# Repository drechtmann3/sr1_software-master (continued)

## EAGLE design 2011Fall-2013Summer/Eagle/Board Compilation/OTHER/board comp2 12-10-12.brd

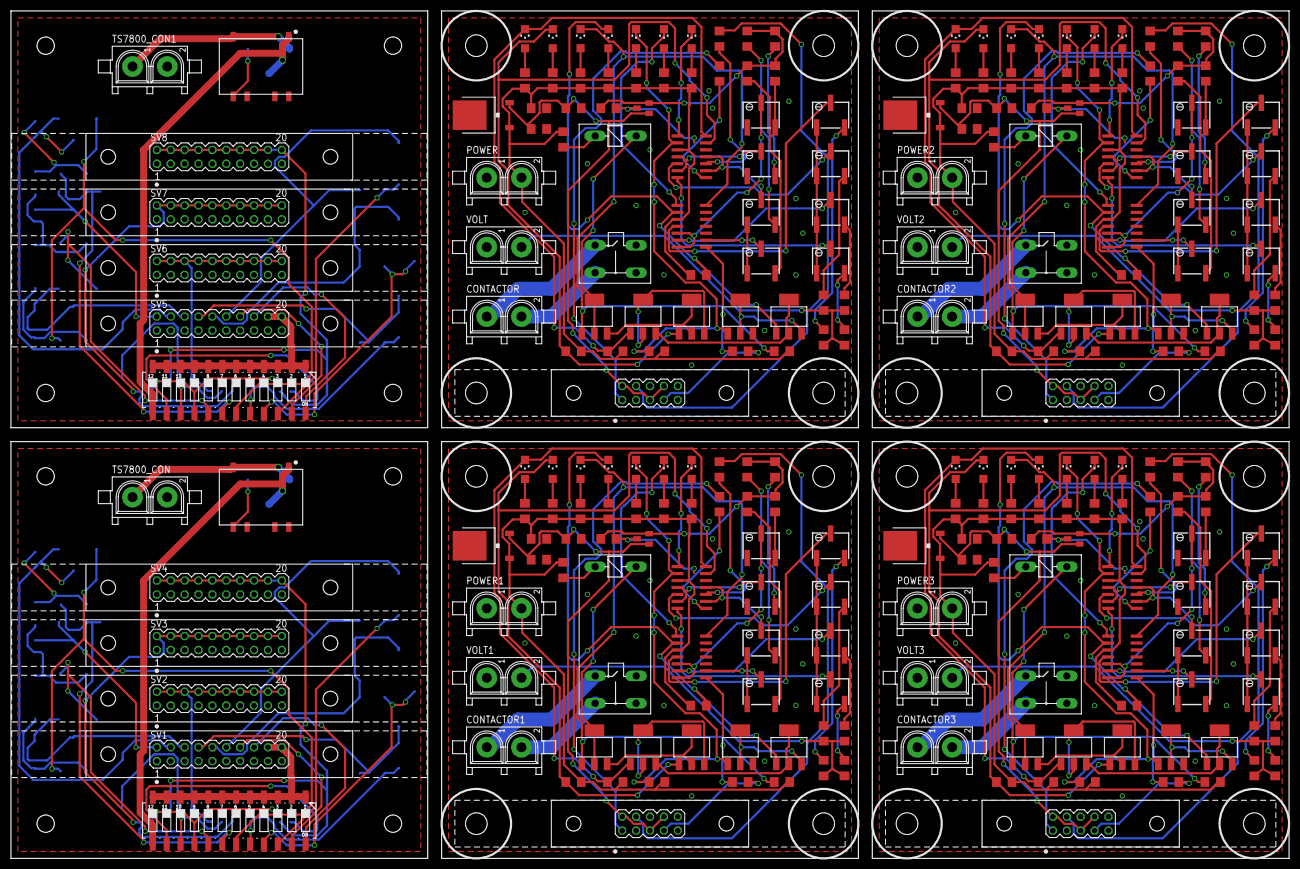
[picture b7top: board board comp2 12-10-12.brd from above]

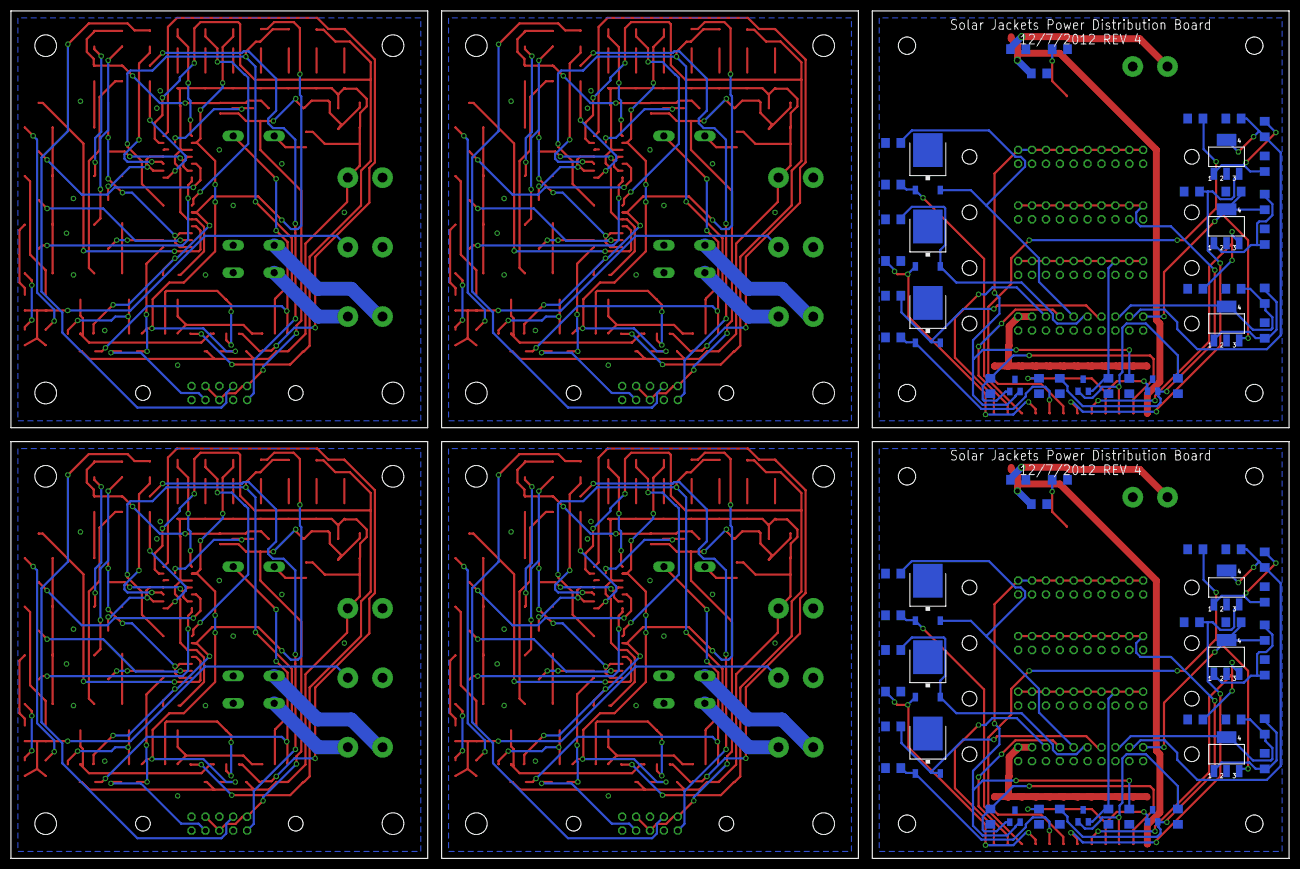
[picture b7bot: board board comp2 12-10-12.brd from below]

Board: 2 copper layers, 233.7 x 154.9 mm, 314 parts (72 on the bottom side), 252 nets.

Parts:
3V1, 3V2, 3V3, 3V4, 3V5, 3V6, 3V7, 3V8, 3V9, 3V10: MAX6103; SOT23
317CAP1, 317CAP3, 317CAP4, 317CAP6, 317CAP9, 317CAP11: .33uF; C1206
317CAP2, 317CAP5, 317CAP7, 317CAP8, 317CAP10, 317CAP12, 6103CAP1, 6103CAP2, 6103CAP3, 6103CAP4, 6103CAP5, 6103CAP6, 6103CAP7, 6103CAP8, 6103CAP9, 6103CAP10, 6103CAP11, 6103CAP12, 6103CAP13, 6103CAP14, 6103CAP15, 6103CAP16, 6103CAP17, 6103CAP18, 6103CAP19, 6103CAP20, 7805CAP1, 7805CAP2, 7805CAP3, 7805CAP4, 7805CAP5, 7805CAP6, 7805CAP7, 7805CAP8: 1uF; C1206
C1, C2, C3, C4, C5, C6, C7, C8, C9, C10, C11, C12: 1uF; C1206
CONTACTOR, CONTACTOR1, CONTACTOR2, CONTACTOR3: 350428-1
CURRENT_TRIM, CURRENT_TRIM1, CURRENT_TRIM2, CURRENT_TRIM3: 1k; RTRIMTS63Y
IC1, IC2, IC3, IC4, IC5, IC6: LM317; SOT223
IC7, IC9, IC10, IC12, IC13, IC15, IC16, IC18: LM339D; SO14
IC8, IC11, IC14, IC17: 7805DT; TO252
K1, K2, K3, K4: G2REA
OVERCURRENT, OVERCURRENT1, OVERCURRENT2, OVERCURRENT3: CHIPLED_1206
OVERCURRENT_FET, OVERCURRENT_FET1, OVERCURRENT_FET2, OVERCURRENT_FET3: N-HEXFET-2D_SOT232-; SOT223
OVERTEMP1, OVERTEMP2, OVERTEMP3, OVERTEMP4, OVERTEMP5, OVERTEMP6, OVERTEMP7, OVERTEMP8: CHIPLED_1206
OVERTEMP1_FET, OVERTEMP1_FET1, OVERTEMP1_FET2, OVERTEMP1_FET3, OVERTEMP2_FET, OVERTEMP2_FET1, OVERTEMP2_FET2, OVERTEMP2_FET3: N-HEXFET-2D_SOT232-; SOT223
OVERVOLT, OVERVOLT1, OVERVOLT2, OVERVOLT3: CHIPLED_1206
OVERVOLT_FET, OVERVOLT_FET1, OVERVOLT_FET2, OVERVOLT_FET3: N-HEXFET-2D_SOT232-; SOT223
OVERVOLT_WARN, OVERVOLT_WARN1, OVERVOLT_WARN2, OVERVOLT_WARN3: CHIPLED_1206
OVER_CRIT, OVER_CRIT1, OVER_CRIT2, OVER_CRIT3: 10k; RTRIMTS63Y
OVER_TRIM, OVER_TRIM1, OVER_TRIM2, OVER_TRIM3: 1k; RTRIMTS63Y
OVER_WARN, OVER_WARN1, OVER_WARN2, OVER_WARN3: 10k; RTRIMTS63Y
POWER, POWER1, POWER2, POWER3: 350428-1
PWR_1, PWR_2, PWR_3, PWR_4, PWR_5, PWR_6: 7805DT; TO252
R1, R3, R5, R7, R9, R11: 220; R1206
R2, R4, R6, R8, R10, R12: 361; R1206
R13, R14, R29, R30, R37, R38, R53, R54, R61, R62, R77, R78, R85, R86, R101, R102: 100k; R1206
R15, R16, R17, R18, R24, R32, R33, R39, R40, R41, R42, R48, R56, R57, R63, R64, R65, R66, R72, R80, R81, R87, R88, R89, R90, R96, R104, R105: 100; R1206
R19, R20, R21, R22, R31, R34, R35, R36, R43, R44, R45, R46, R55, R58, R59, R60, R67, R68, R69, R70, R79, R82, R83, R84, R91, R92, R93, R94, R103, R106, R107, R108: 1k; R1206
R23, R25, R26, R27, R28, R47, R49, R50, R51, R52, R71, R73, R74, R75, R76, R95, R97, R98, R99, R100: 10k; R1206
S1, S2: 219-12; CTS-219-12
SV1, SV2, SV3, SV4, SV5, SV6, SV7, SV8: AMPLATCH-20; MA10-2
SV9, SV10, SV11, SV12: AMP_LATCH_10; MA05-2
TEMP_TRIM, TEMP_TRIM1, TEMP_TRIM2, TEMP_TRIM3: 1k; RTRIMTS63Y
TS7800_CON, TS7800_CON1: 350759-4
U$1, U$2: V7805
UNDERVOLT, UNDERVOLT1, UNDERVOLT2, UNDERVOLT3: CHIPLED_1206
UNDERVOLT_FET, UNDERVOLT_FET1, UNDERVOLT_FET2, UNDERVOLT_FET3: N-HEXFET-2D_SOT232-; SOT223
UNDERVOLT_WARN, UNDERVOLT_WARN1, UNDERVOLT_WARN2, UNDERVOLT_WARN3: CHIPLED_1206
UNDER_CRIT, UNDER_CRIT1, UNDER_CRIT2, UNDER_CRIT3: 10k; RTRIMTS63Y
UNDER_TRIM, UNDER_TRIM1, UNDER_TRIM2, UNDER_TRIM3: 1k; RTRIMTS63Y
UNDER_WARN, UNDER_WARN1, UNDER_WARN2, UNDER_WARN3: 10k; RTRIMTS63Y
V7805_C1, V7805_C2, V7805_C3, V7805_C4, V7805_C5, V7805_C6: 1uF; C1206
VOLT, VOLT1, VOLT2, VOLT3: 350428-1

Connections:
3.3V1: 317CAP8.1, IC4.4, R7.1, SV1.6
3.3V1_EN: 317CAP3.1, IC4.3, S1.19
3.3V1_EN1: 317CAP1.1, IC1.3, S2.19
3.3V2: 317CAP10.1, IC5.4, R9.1, SV1.4
3.3V2_EN: 317CAP9.1, IC5.3, S1.18
3.3V2_EN1: 317CAP4.1, IC2.3, S2.18
3.3V3: 317CAP12.1, IC6.4, R11.1, SV1.2
3.3V3_EN: 317CAP11.1, IC6.3, S1.17
3.3V3_EN1: 317CAP6.1, IC3.3, S2.17
3.3V4: 317CAP7.1, IC3.4, R5.1, SV5.2
3.3V5: 317CAP2.1, IC1.4, R1.1, SV5.6
3.3V6: 317CAP5.1, IC2.4, R3.1, SV5.4
5V: 3V7.1, 6103CAP13.1, 7805CAP2.1, IC8.2, SV9.2, SV9.5, SV9.8
5V1: C2.1, PWR_1.2, SV1.12
5V1_EN: C1.1, PWR_1.1, S1.22
5V1_EN1: C7.1, PWR_4.1, S2.22
5V2: C4.1, PWR_2.2, SV1.10
5V2_EN: C3.1, PWR_2.1, S1.21
5V2_EN1: C9.1, PWR_5.1, S2.21
5V3: C6.1, PWR_3.2, SV1.8
5V3_EN: C5.1, PWR_3.1, S1.20
5V3_EN1: C12.1, PWR_6.1, S2.20
5V4: C11.1, PWR_6.2, SV5.8
5V5: C10.1, PWR_5.2, SV5.10
5V6: C8.1, PWR_4.2, SV5.12
5V7: 3V8.1, 6103CAP15.1, 7805CAP3.1, IC11.2, SV10.2, SV10.5, SV10.8
5V8: 3V9.1, 6103CAP17.1, 7805CAP5.1, IC14.2, SV11.2, SV11.5, SV11.8
5V9: 3V10.1, 6103CAP19.1, 7805CAP7.1, IC17.2, SV12.2, SV12.5, SV12.8
12V: S1.1, S1.2, S1.3, S1.4, S1.5, S1.6, S1.7, S1.8, S1.9, S1.10, S1.11, S1.12, SV1.18, SV1.20
12V1: S2.1, S2.2, S2.3, S2.4, S2.5, S2.6, S2.7, S2.8, S2.9, S2.10, S2.11, S2.12, SV5.18, SV5.20
12V1_EN: S1.24, SV1.16
12V1_EN1: S2.24, SV5.16
12V2: 7805CAP1.1, IC7.3, IC8.1, IC9.3, POWER.2, R19.2, R20.2, R21.2, R22.2, R23.2, R24.2, R25.2, R26.2, R27.2, R28.2, R34.2, R35.2, R36.2
12V2_EN: S1.23, SV1.14
12V2_EN1: S2.23, SV5.14
12V3: 7805CAP4.1, IC10.3, IC11.1, IC12.3, POWER1.2, R43.2, R44.2, R45.2, R46.2, R47.2, R48.2, R49.2, R50.2, R51.2, R52.2, R58.2, R59.2, R60.2
12V4: 7805CAP6.1, IC13.3, IC14.1, IC15.3, POWER2.2, R67.2, R68.2, R69.2, R70.2, R71.2, R72.2, R73.2, R74.2, R75.2, R76.2, R82.2, R83.2, R84.2
12V5: 7805CAP8.1, IC16.3, IC17.1, IC18.3, POWER3.2, R91.2, R92.2, R93.2, R94.2, R95.2, R96.2, R97.2, R98.2, R99.2, R100.2, R106.2, R107.2, R108.2
96V: R13.2, R14.2, R29.2, R30.2, VOLT.2
96V1: R37.2, R38.2, R53.2, R54.2, VOLT1.2
96V2: R61.2, R62.2, R77.2, R78.2, VOLT2.2
96V3: R85.2, R86.2, R101.2, R102.2, VOLT3.2
CONTACTOR_IN: CONTACTOR.2, K1.S
CONTACTOR_IN1: CONTACTOR1.2, K2.S
CONTACTOR_IN2: CONTACTOR2.2, K3.S
CONTACTOR_IN3: CONTACTOR3.2, K4.S
CONTACTOR_OUT: CONTACTOR.1, K1.P
CONTACTOR_OUT1: CONTACTOR1.1, K2.P
CONTACTOR_OUT2: CONTACTOR2.1, K3.P
CONTACTOR_OUT3: CONTACTOR3.1, K4.P
CURRENT: R31.2, SV9.7
CURRENT1: R55.2, SV10.7
CURRENT2: R79.2, SV11.7
CURRENT3: R103.2, SV12.7
GND: 3V3.3, 3V4.3, 3V5.3, 317CAP3.2, 317CAP8.2, 317CAP9.2, 317CAP10.2, 317CAP11.2, 317CAP12.2, 6103CAP7.2, 6103CAP8.2, 6103CAP9.2, 6103CAP10.2, 6103CAP11.2, 6103CAP12.2, C1.2, C2.2, C3.2, C4.2, C5.2, C6.2, PWR_1.3, PWR_2.3, PWR_3.3, R8.2, R10.2, R12.2, SV1.1, SV1.3, SV1.5, SV1.7, SV1.9, SV1.11, SV1.13, SV1.15, SV1.17, SV1.19, SV2.1, SV2.3, SV2.5, SV2.7, SV2.9, SV2.11, SV2.13, SV2.15, SV2.17, SV2.19, SV3.1, SV3.3, SV3.5, SV3.7, SV3.9, SV3.11, SV3.13, SV3.15, SV3.17, SV3.19, SV4.1, SV4.3, SV4.5, SV4.7, SV4.9, SV4.11, SV4.13, SV4.15, SV4.17, SV4.19, TS7800_CON.2, U$2.7, U$2.9, V7805_C4.2, V7805_C5.2, V7805_C6.2
GND1: 3V1.3, 3V2.3, 3V6.3, 317CAP1.2, 317CAP2.2, 317CAP4.2, 317CAP5.2, 317CAP6.2, 317CAP7.2, 6103CAP1.2, 6103CAP2.2, 6103CAP3.2, 6103CAP4.2, 6103CAP5.2, 6103CAP6.2, C7.2, C8.2, C9.2, C10.2, C11.2, C12.2, PWR_4.3, PWR_5.3, PWR_6.3, R2.2, R4.2, R6.2, SV5.1, SV5.3, SV5.5, SV5.7, SV5.9, SV5.11, SV5.13, SV5.15, SV5.17, SV5.19, SV6.1, SV6.3, SV6.5, SV6.7, SV6.9, SV6.11, SV6.13, SV6.15, SV6.17, SV6.19, SV7.1, SV7.3, SV7.5, SV7.7, SV7.9, SV7.11, SV7.13, SV7.15, SV7.17, SV7.19, SV8.1, SV8.3, SV8.5, SV8.7, SV8.9, SV8.11, SV8.13, SV8.15, SV8.17, SV8.19, TS7800_CON1.2, U$1.7, U$1.9, V7805_C1.2, V7805_C2.2, V7805_C3.2
GND2: 3V7.3, 6103CAP13.2, 6103CAP14.2, 7805CAP1.2, 7805CAP2.2, CURRENT_TRIM.1, IC7.12, IC8.3, IC9.12, OVER_CRIT.1, OVER_TRIM.1, OVER_WARN.1, POWER.1, SV9.3, SV9.6, SV9.9, TEMP_TRIM.1, UNDERVOLT_FET.3, UNDER_CRIT.1, UNDER_TRIM.1, UNDER_WARN.1, VOLT.1
GND3: 3V8.3, 6103CAP15.2, 6103CAP16.2, 7805CAP3.2, 7805CAP4.2, CURRENT_TRIM1.1, IC10.12, IC11.3, IC12.12, OVER_CRIT1.1, OVER_TRIM1.1, OVER_WARN1.1, POWER1.1, SV10.3, SV10.6, SV10.9, TEMP_TRIM1.1, UNDERVOLT_FET1.3, UNDER_CRIT1.1, UNDER_TRIM1.1, UNDER_WARN1.1, VOLT1.1
GND4: 3V9.3, 6103CAP17.2, 6103CAP18.2, 7805CAP5.2, 7805CAP6.2, CURRENT_TRIM2.1, IC13.12, IC14.3, IC15.12, OVER_CRIT2.1, OVER_TRIM2.1, OVER_WARN2.1, POWER2.1, SV11.3, SV11.6, SV11.9, TEMP_TRIM2.1, UNDERVOLT_FET2.3, UNDER_CRIT2.1, UNDER_TRIM2.1, UNDER_WARN2.1, VOLT2.1
GND5: 3V10.3, 6103CAP19.2, 6103CAP20.2, 7805CAP7.2, 7805CAP8.2, CURRENT_TRIM3.1, IC16.12, IC17.3, IC18.12, OVER_CRIT3.1, OVER_TRIM3.1, OVER_WARN3.1, POWER3.1, SV12.3, SV12.6, SV12.9, TEMP_TRIM3.1, UNDERVOLT_FET3.3, UNDER_CRIT3.1, UNDER_TRIM3.1, UNDER_WARN3.1, VOLT3.1
unnamed: U$2.6, V7805_C4.1
unnamed: IC1.1, R1.2, R2.1
unnamed: IC2.1, R3.2, R4.1
unnamed: IC3.1, R5.2, R6.1
unnamed: U$1.6, V7805_C1.1
unnamed: IC7.7, UNDER_WARN.2
unnamed: IC7.5, UNDER_CRIT.2
unnamed: IC7.9, IC7.11, TEMP_TRIM.2
unnamed: R13.1, UNDER_CRIT.3
unnamed: R14.1, UNDER_WARN.3
unnamed: IC7.4, IC7.6, UNDER_TRIM.2
unnamed: IC4.1, R7.2, R8.1
unnamed: IC5.1, R9.2, R10.1
unnamed: IC6.1, R11.2, R12.1
unnamed: R18.1, UNDER_TRIM.3
unnamed: R17.1, TEMP_TRIM.3
unnamed: R19.1, UNDERVOLT.A
unnamed: R20.1, UNDERVOLT_WARN.A
unnamed: OVERTEMP1.A, R21.1
unnamed: OVERTEMP2.A, R22.1
unnamed: IC7.8, R15.1
unnamed: IC7.10, R16.1
unnamed: CURRENT_TRIM.2, IC9.9
unnamed: OVER_WARN.3, R30.1
unnamed: IC9.6, OVER_WARN.2
unnamed: IC9.4, OVER_CRIT.2
unnamed: IC9.5, IC9.7, OVER_TRIM.2
unnamed: OVER_TRIM.3, R33.1
unnamed: CURRENT_TRIM.3, R32.1
unnamed: OVERVOLT.A, R34.1
unnamed: OVERVOLT_WARN.A, R35.1
unnamed: OVERCURRENT.A, R36.1
unnamed: OVER_CRIT.3, R29.1
unnamed: IC9.8, R31.1
unnamed: K1.1, R24.1
unnamed: K1.2, OVERCURRENT_FET.2, OVERCURRENT_FET.4
unnamed: OVERCURRENT_FET.3, OVERTEMP2_FET.2, OVERTEMP2_FET.4
unnamed: OVERTEMP1_FET.2, OVERTEMP1_FET.4, OVERTEMP2_FET.3
unnamed: OVERTEMP1_FET.3, OVERVOLT_FET.2, OVERVOLT_FET.4
unnamed: OVERVOLT_FET.3, UNDERVOLT_FET.2, UNDERVOLT_FET.4
unnamed: IC10.7, UNDER_WARN1.2
unnamed: IC10.5, UNDER_CRIT1.2
unnamed: IC10.9, IC10.11, TEMP_TRIM1.2
unnamed: R37.1, UNDER_CRIT1.3
unnamed: R38.1, UNDER_WARN1.3
unnamed: IC10.4, IC10.6, UNDER_TRIM1.2
unnamed: R42.1, UNDER_TRIM1.3
unnamed: R41.1, TEMP_TRIM1.3
unnamed: R43.1, UNDERVOLT1.A
unnamed: R44.1, UNDERVOLT_WARN1.A
unnamed: OVERTEMP3.A, R45.1
unnamed: OVERTEMP4.A, R46.1
unnamed: IC10.8, R39.1
unnamed: IC10.10, R40.1
unnamed: CURRENT_TRIM1.2, IC12.9
unnamed: OVER_WARN1.3, R54.1
unnamed: IC12.5, IC12.7, OVER_TRIM1.2
unnamed: OVER_TRIM1.3, R57.1
unnamed: CURRENT_TRIM1.3, R56.1
unnamed: OVERVOLT1.A, R58.1
unnamed: OVERVOLT_WARN1.A, R59.1
unnamed: OVERCURRENT1.A, R60.1
unnamed: IC12.6, OVER_WARN1.2
unnamed: IC12.4, OVER_CRIT1.2
unnamed: OVER_CRIT1.3, R53.1
unnamed: IC12.8, R55.1
unnamed: K2.1, R48.1
unnamed: K2.2, OVERCURRENT_FET1.2, OVERCURRENT_FET1.4
unnamed: OVERCURRENT_FET1.3, OVERTEMP2_FET1.2, OVERTEMP2_FET1.4
unnamed: OVERTEMP1_FET1.2, OVERTEMP1_FET1.4, OVERTEMP2_FET1.3
unnamed: OVERTEMP1_FET1.3, OVERVOLT_FET1.2, OVERVOLT_FET1.4
unnamed: OVERVOLT_FET1.3, UNDERVOLT_FET1.2, UNDERVOLT_FET1.4
unnamed: IC13.7, UNDER_WARN2.2
unnamed: IC13.5, UNDER_CRIT2.2
unnamed: IC13.9, IC13.11, TEMP_TRIM2.2
unnamed: R61.1, UNDER_CRIT2.3
unnamed: R62.1, UNDER_WARN2.3
unnamed: IC13.4, IC13.6, UNDER_TRIM2.2
unnamed: R66.1, UNDER_TRIM2.3
unnamed: R65.1, TEMP_TRIM2.3
unnamed: R67.1, UNDERVOLT2.A
unnamed: R68.1, UNDERVOLT_WARN2.A
unnamed: OVERTEMP5.A, R69.1
unnamed: OVERTEMP6.A, R70.1
unnamed: IC13.8, R63.1
unnamed: IC13.10, R64.1
unnamed: CURRENT_TRIM2.2, IC15.9
unnamed: OVER_WARN2.3, R78.1
unnamed: IC15.5, IC15.7, OVER_TRIM2.2
unnamed: OVER_TRIM2.3, R81.1
unnamed: CURRENT_TRIM2.3, R80.1
unnamed: OVERVOLT2.A, R82.1
unnamed: OVERVOLT_WARN2.A, R83.1
unnamed: OVERCURRENT2.A, R84.1
unnamed: IC15.6, OVER_WARN2.2
unnamed: IC15.4, OVER_CRIT2.2
unnamed: OVER_CRIT2.3, R77.1
unnamed: IC15.8, R79.1
unnamed: K3.1, R72.1
unnamed: K3.2, OVERCURRENT_FET2.2, OVERCURRENT_FET2.4
unnamed: OVERCURRENT_FET2.3, OVERTEMP2_FET2.2, OVERTEMP2_FET2.4
unnamed: OVERTEMP1_FET2.2, OVERTEMP1_FET2.4, OVERTEMP2_FET2.3
unnamed: OVERTEMP1_FET2.3, OVERVOLT_FET2.2, OVERVOLT_FET2.4
unnamed: OVERVOLT_FET2.3, UNDERVOLT_FET2.2, UNDERVOLT_FET2.4
unnamed: IC16.7, UNDER_WARN3.2
unnamed: IC16.5, UNDER_CRIT3.2
unnamed: IC16.9, IC16.11, TEMP_TRIM3.2
unnamed: R85.1, UNDER_CRIT3.3
unnamed: R86.1, UNDER_WARN3.3
unnamed: IC16.4, IC16.6, UNDER_TRIM3.2
unnamed: R90.1, UNDER_TRIM3.3
unnamed: R89.1, TEMP_TRIM3.3
unnamed: R91.1, UNDERVOLT3.A
unnamed: R92.1, UNDERVOLT_WARN3.A
unnamed: OVERTEMP7.A, R93.1
unnamed: OVERTEMP8.A, R94.1
unnamed: IC16.8, R87.1
unnamed: IC16.10, R88.1
unnamed: CURRENT_TRIM3.2, IC18.9
unnamed: OVER_WARN3.3, R102.1
unnamed: IC18.5, IC18.7, OVER_TRIM3.2
unnamed: OVER_TRIM3.3, R105.1
unnamed: CURRENT_TRIM3.3, R104.1
unnamed: OVERVOLT3.A, R106.1
unnamed: OVERVOLT_WARN3.A, R107.1
unnamed: OVERCURRENT3.A, R108.1
unnamed: IC18.6, OVER_WARN3.2
unnamed: IC18.4, OVER_CRIT3.2
unnamed: OVER_CRIT3.3, R101.1
unnamed: IC18.8, R103.1
unnamed: K4.1, R96.1
unnamed: K4.2, OVERCURRENT_FET3.2, OVERCURRENT_FET3.4
unnamed: OVERCURRENT_FET3.3, OVERTEMP2_FET3.2, OVERTEMP2_FET3.4
unnamed: OVERTEMP1_FET3.2, OVERTEMP1_FET3.4, OVERTEMP2_FET3.3
unnamed: OVERTEMP1_FET3.3, OVERVOLT_FET3.2, OVERVOLT_FET3.4
unnamed: OVERVOLT_FET3.3, UNDERVOLT_FET3.2, UNDERVOLT_FET3.4
OVERCURRENT_CRITICAL: IC9.14, OVERCURRENT.C, OVERCURRENT_FET.1, R28.1
OVERCURRENT_CRITICAL1: IC12.14, OVERCURRENT1.C, OVERCURRENT_FET1.1, R52.1
OVERCURRENT_CRITICAL2: IC15.14, OVERCURRENT2.C, OVERCURRENT_FET2.1, R76.1
OVERCURRENT_CRITICAL3: IC18.14, OVERCURRENT3.C, OVERCURRENT_FET3.1, R100.1
OVERTEMP_CRITICAL1: IC7.14, OVERTEMP1.C, OVERTEMP1_FET.1, R26.1
OVERTEMP_CRITICAL2: IC7.13, OVERTEMP2.C, OVERTEMP2_FET.1, R27.1
OVERTEMP_CRITICAL3: IC10.14, OVERTEMP1_FET1.1, OVERTEMP3.C, R50.1
OVERTEMP_CRITICAL4: IC10.13, OVERTEMP2_FET1.1, OVERTEMP4.C, R51.1
OVERTEMP_CRITICAL5: IC13.14, OVERTEMP1_FET2.1, OVERTEMP5.C, R74.1
OVERTEMP_CRITICAL6: IC13.13, OVERTEMP2_FET2.1, OVERTEMP6.C, R75.1
OVERTEMP_CRITICAL7: IC16.14, OVERTEMP1_FET3.1, OVERTEMP7.C, R98.1
OVERTEMP_CRITICAL8: IC16.13, OVERTEMP2_FET3.1, OVERTEMP8.C, R99.1
OVERVOLT_CRITICAL: IC9.2, OVERVOLT.C, OVERVOLT_FET.1, R25.1
OVERVOLT_CRITICAL1: IC12.2, OVERVOLT1.C, OVERVOLT_FET1.1, R49.1
OVERVOLT_CRITICAL2: IC15.2, OVERVOLT2.C, OVERVOLT_FET2.1, R73.1
OVERVOLT_CRITICAL3: IC18.2, OVERVOLT3.C, OVERVOLT_FET3.1, R97.1
OVERVOLT_WARNING1: IC9.1, OVERVOLT_WARN.C
OVERVOLT_WARNING2: IC12.1, OVERVOLT_WARN1.C
OVERVOLT_WARNING3: IC15.1, OVERVOLT_WARN2.C
OVERVOLT_WARNING4: IC18.1, OVERVOLT_WARN3.C
TEMP1: R15.2, SV9.1
TEMP2: R16.2, SV9.4
TEMP3: R39.2, SV10.1
TEMP4: R40.2, SV10.4
TEMP5: R63.2, SV11.1
TEMP6: R64.2, SV11.4
TEMP7: R87.2, SV12.1
TEMP8: R88.2, SV12.4
TS7800_+: TS7800_CON.1, U$2.5, V7805_C6.1
TS7800_+1: TS7800_CON1.1, U$1.5, V7805_C3.1
TS7800_EN: S1.13, U$2.1, V7805_C5.1
TS7800_EN1: S2.13, U$1.1, V7805_C2.1
UNDERVOLT_CRITICAL: IC7.2, R23.1, UNDERVOLT.C, UNDERVOLT_FET.1
UNDERVOLT_CRITICAL1: IC10.2, R47.1, UNDERVOLT1.C, UNDERVOLT_FET1.1
UNDERVOLT_CRITICAL2: IC13.2, R71.1, UNDERVOLT2.C, UNDERVOLT_FET2.1
UNDERVOLT_CRITICAL3: IC16.2, R95.1, UNDERVOLT3.C, UNDERVOLT_FET3.1
UNDERVOLT_WARNING: IC7.1, UNDERVOLT_WARN.C
UNDERVOLT_WARNING1: IC10.1, UNDERVOLT_WARN1.C
UNDERVOLT_WARNING2: IC13.1, UNDERVOLT_WARN2.C
UNDERVOLT_WARNING3: IC16.1, UNDERVOLT_WARN3.C
VREF: 3V7.2, 6103CAP14.1, R17.2, R18.2, R32.2, R33.2
VREF1: 3V3.2, 6103CAP8.1, SV3.2, SV3.4, SV3.6, SV3.8, SV3.10, SV3.12, SV3.14, SV3.16, SV3.18, SV3.20
VREF1_EN: 3V3.1, 6103CAP7.1, S1.16
VREF1_EN1: 3V1.1, 6103CAP1.1, S2.16
VREF2: 3V4.2, 6103CAP10.1, SV2.2, SV2.4, SV2.6, SV2.8, SV2.10, SV2.12, SV2.14, SV2.16, SV2.18, SV2.20
VREF2_EN: 3V4.1, 6103CAP9.1, S1.15
VREF2_EN1: 3V2.1, 6103CAP3.1, S2.15
VREF3: 3V5.2, 6103CAP12.1, SV4.2, SV4.4, SV4.6, SV4.8, SV4.10, SV4.12, SV4.14, SV4.16, SV4.18, SV4.20
VREF3_EN: 3V5.1, 6103CAP11.1, S1.14
VREF3_EN1: 3V6.1, 6103CAP5.1, S2.14
VREF4: 3V1.2, 6103CAP2.1, SV7.2, SV7.4, SV7.6, SV7.8, SV7.10, SV7.12, SV7.14, SV7.16, SV7.18, SV7.20
VREF5: 3V2.2, 6103CAP4.1, SV6.2, SV6.4, SV6.6, SV6.8, SV6.10, SV6.12, SV6.14, SV6.16, SV6.18, SV6.20
VREF6: 3V6.2, 6103CAP6.1, SV8.2, SV8.4, SV8.6, SV8.8, SV8.10, SV8.12, SV8.14, SV8.16, SV8.18, SV8.20
VREF7: 3V8.2, 6103CAP16.1, R41.2, R42.2, R56.2, R57.2
VREF8: 3V9.2, 6103CAP18.1, R65.2, R66.2, R80.2, R81.2
VREF9: 3V10.2, 6103CAP20.1, R89.2, R90.2, R104.2, R105.2

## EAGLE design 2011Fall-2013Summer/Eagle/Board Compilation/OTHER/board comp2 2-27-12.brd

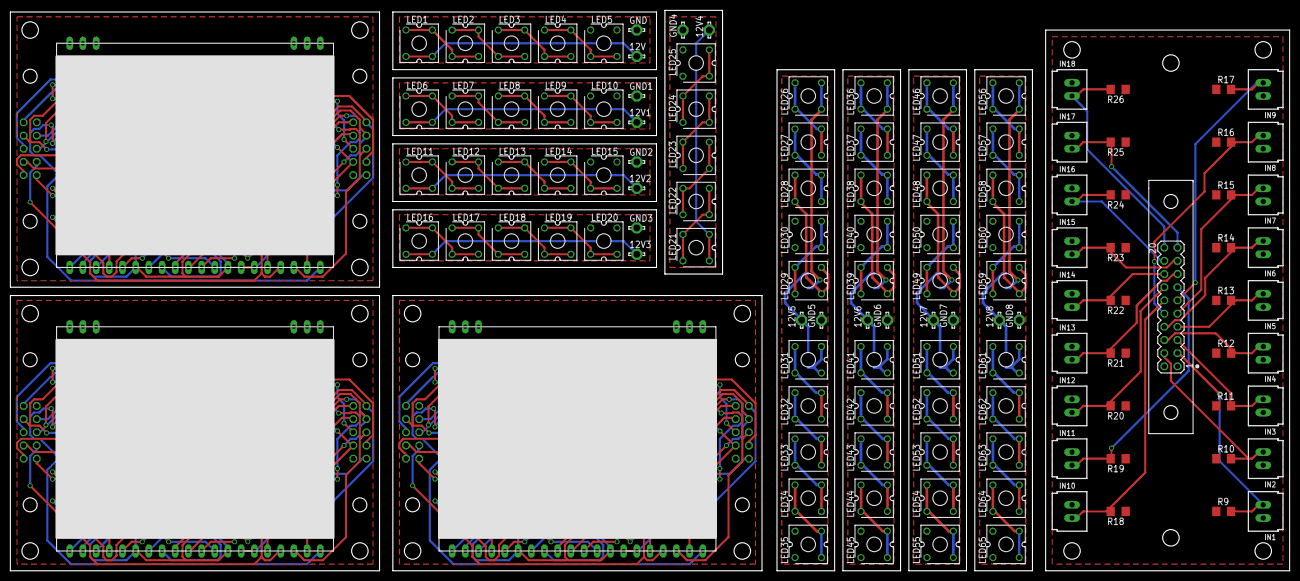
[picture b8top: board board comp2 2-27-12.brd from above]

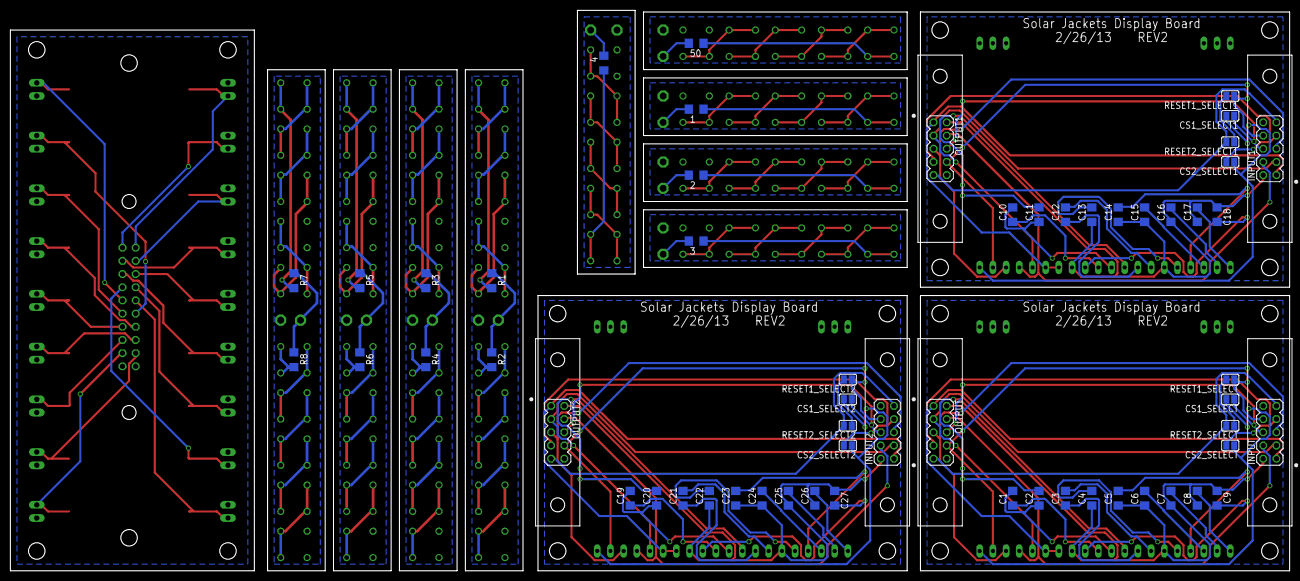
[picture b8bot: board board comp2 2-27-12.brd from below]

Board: 2 copper layers, 246.4 x 107.9 mm, 181 parts (58 on the bottom side), 169 nets.

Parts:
1, 2, 3, 4, 50: RESISTORSMD1206; R1206
12V, 12V1, 12V2, 12V3, 12V4, 12V5, 12V6, 12V7, 12V8: LSP13
C1, C2, C3, C4, C5, C6, C7, C8, C9, C10, C11, C12, C13, C14, C15, C16, C17, C18, C19, C20, C21, C22, C23, C24, C25, C26, C27: 1uF; C1206
CS1_SELECT, CS1_SELECT1, CS1_SELECT2, CS2_SELECT, CS2_SELECT1, CS2_SELECT2: SJ
GND, GND1, GND2, GND3, GND4, GND5, GND6, GND7, GND8: LSP13
IC1, IC2, IC3: EADOGM128
IN1, IN2, IN3, IN4, IN5, IN6, IN7, IN8, IN9, IN10, IN11, IN12, IN13, IN14, IN15, IN16, IN17, IN18: C-GRID-02-70543; 70543-02
INPUT, INPUT1, INPUT2: AMP_LATCH_10; MA05-2
LED1, LED6, LED11, LED16, LED21, LED26, LED36, LED46, LED56: LED1; CP41B
LED2, LED7, LED12, LED17, LED22, LED27, LED37, LED47, LED57: LED2; CP41B
LED3, LED8, LED13, LED18, LED23, LED28, LED38, LED48, LED58: LED3; CP41B
LED4, LED9, LED14, LED19, LED24, LED29, LED39, LED49, LED59: LED4; CP41B
LED5, LED10, LED15, LED20, LED25, LED30, LED40, LED50, LED60: LED5; CP41B
LED31, LED41, LED51, LED61: LED6; CP41B
LED32, LED42, LED52, LED62: LED7; CP41B
LED33, LED43, LED53, LED63: LED8; CP41B
LED34, LED44, LED54, LED64: LED9; CP41B
LED35, LED45, LED55, LED65: LED10; CP41B
OUTPUT, OUTPUT1, OUTPUT2: AMP_LATCH_10; MA05-2
R1, R2, R3, R4, R5, R6, R7, R8: 50; R1206
R9, R10, R11, R12, R13, R14, R15, R16, R17, R18, R19, R20, R21, R22, R23, R24, R25, R26: 1K; R1206
RESET1_SELECT, RESET1_SELECT1, RESET1_SELECT2, RESET2_SELECT, RESET2_SELECT1, RESET2_SELECT2: SJ
U$1: AMP_LATCH-20; MA10-2

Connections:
3.3V: IC1.34, IC1.35, INPUT.1, OUTPUT.1
3.3V1: IC2.34, IC2.35, INPUT1.1, OUTPUT1.1
3.3V2: IC3.34, IC3.35, INPUT2.1, OUTPUT2.1
3.3V3: IN1.1, IN2.1, IN3.1, IN4.1, IN5.1, IN6.1, IN7.1, IN8.1, IN9.1, IN10.1, IN11.1, IN12.1, IN13.1, IN14.1, IN15.1, IN16.1, IN17.1, IN18.1, U$1.1
A0: IC1.38, INPUT.5, OUTPUT.5
A1: IC2.38, INPUT1.5, OUTPUT1.5
A2: IC3.38, INPUT2.5, OUTPUT2.5
CS1: CS1_SELECT.1, INPUT.6, OUTPUT.6
CS2: CS2_SELECT.2, INPUT.7, OUTPUT.7
CS3: CS1_SELECT1.1, INPUT1.6, OUTPUT1.6
CS4: CS2_SELECT1.2, INPUT1.7, OUTPUT1.7
CS5: CS1_SELECT2.1, INPUT2.6, OUTPUT2.6
CS6: CS2_SELECT2.2, INPUT2.7, OUTPUT2.7
CS_SLCT: CS1_SELECT.2, CS2_SELECT.1, IC1.40
CS_SLCT1: CS1_SELECT1.2, CS2_SELECT1.1, IC2.40
CS_SLCT2: CS1_SELECT2.2, CS2_SELECT2.1, IC3.40
GND: C4.1, C5.1, C6.1, C7.1, C8.1, C9.1, IC1.26, IC1.33, INPUT.2, OUTPUT.2
GND1: C13.1, C14.1, C15.1, C16.1, C17.1, C18.1, IC2.26, IC2.33, INPUT1.2, OUTPUT1.2
GND2: C22.1, C23.1, C24.1, C25.1, C26.1, C27.1, IC3.26, IC3.33, INPUT2.2, OUTPUT2.2
GND3: GND.MP, LED5.1, LED5.4
GND4: GND1.MP, LED10.1, LED10.4
GND5: GND2.MP, LED15.1, LED15.4
GND6: GND3.MP, LED20.1, LED20.4
GND7: GND4.MP, LED25.1, LED25.4
GND8: GND5.MP, LED30.1, LED30.4, LED35.1, LED35.4
GND9: GND6.MP, LED40.1, LED40.4, LED45.1, LED45.4
GND10: GND7.MP, LED50.1, LED50.4, LED55.1, LED55.4
GND11: GND8.MP, LED60.1, LED60.4, LED65.1, LED65.4
GND12: R9.1, R10.1, R11.1, R12.1, R13.1, R14.1, R15.1, R16.1, R17.1, R18.1, R19.1, R20.1, R21.1, R22.1, R23.1, R24.1, R25.1, R26.1, U$1.2
IN1: IN1.2, R9.2, U$1.3
IN2: IN2.2, R10.2, U$1.4
IN3: IN3.2, R11.2, U$1.5
IN4: IN4.2, R12.2, U$1.6
IN5: IN5.2, R13.2, U$1.7
IN6: IN6.2, R14.2, U$1.8
IN7: IN7.2, R15.2, U$1.9
IN8: IN8.2, R16.2, U$1.10
IN9: IN9.2, R17.2, U$1.11
IN10: IN10.2, R18.2, U$1.12
IN11: IN11.2, R19.2, U$1.13
IN12: IN12.2, R20.2, U$1.14
IN13: IN13.2, R21.2, U$1.15
IN14: IN14.2, R22.2, U$1.16
IN15: IN15.2, R23.2, U$1.17
IN16: IN16.2, R24.2, U$1.18
IN17: IN17.2, R25.2, U$1.19
IN18: IN18.2, R26.2, U$1.20
unnamed: C1.2, C2.1, IC1.30
unnamed: C1.1, IC1.31
unnamed: C2.2, IC1.29
unnamed: C3.2, IC1.27
unnamed: C3.1, IC1.28
unnamed: C9.2, IC1.32
unnamed: C4.2, IC1.25
unnamed: C5.2, IC1.24
unnamed: C6.2, IC1.23
unnamed: C7.2, IC1.22
unnamed: C8.2, IC1.21
unnamed: C10.2, C11.1, IC2.30
unnamed: C10.1, IC2.31
unnamed: C11.2, IC2.29
unnamed: C12.2, IC2.27
unnamed: C12.1, IC2.28
unnamed: C13.2, IC2.25
unnamed: C14.2, IC2.24
unnamed: C15.2, IC2.23
unnamed: C16.2, IC2.22
unnamed: C17.2, IC2.21
unnamed: C18.2, IC2.32
unnamed: C19.2, C20.1, IC3.30
unnamed: C19.1, IC3.31
unnamed: C20.2, IC3.29
unnamed: C21.2, IC3.27
unnamed: C21.1, IC3.28
unnamed: C22.2, IC3.25
unnamed: C23.2, IC3.24
unnamed: C24.2, IC3.23
unnamed: C25.2, IC3.22
unnamed: C26.2, IC3.21
unnamed: C27.2, IC3.32
unnamed: 50.2, LED1.2, LED1.3
unnamed: LED1.1, LED1.4, LED2.2, LED2.3
unnamed: LED2.1, LED2.4, LED3.2, LED3.3
unnamed: LED3.1, LED3.4, LED4.2, LED4.3
unnamed: LED4.1, LED4.4, LED5.2, LED5.3
unnamed: 12V.MP, 50.1
unnamed: 1.2, LED6.2, LED6.3
unnamed: LED6.1, LED6.4, LED7.2, LED7.3
unnamed: LED7.1, LED7.4, LED8.2, LED8.3
unnamed: LED8.1, LED8.4, LED9.2, LED9.3
unnamed: LED9.1, LED9.4, LED10.2, LED10.3
unnamed: 1.1, 12V1.MP
unnamed: 2.2, LED11.2, LED11.3
unnamed: LED11.1, LED11.4, LED12.2, LED12.3
unnamed: LED12.1, LED12.4, LED13.2, LED13.3
unnamed: LED13.1, LED13.4, LED14.2, LED14.3
unnamed: LED14.1, LED14.4, LED15.2, LED15.3
unnamed: 2.1, 12V2.MP
unnamed: 3.2, LED16.2, LED16.3
unnamed: LED16.1, LED16.4, LED17.2, LED17.3
unnamed: LED17.1, LED17.4, LED18.2, LED18.3
unnamed: LED18.1, LED18.4, LED19.2, LED19.3
unnamed: LED19.1, LED19.4, LED20.2, LED20.3
unnamed: 3.1, 12V3.MP
unnamed: 4.2, LED21.2, LED21.3
unnamed: LED21.1, LED21.4, LED22.2, LED22.3
unnamed: LED22.1, LED22.4, LED23.2, LED23.3
unnamed: LED23.1, LED23.4, LED24.2, LED24.3
unnamed: LED24.1, LED24.4, LED25.2, LED25.3
unnamed: 4.1, 12V4.MP
unnamed: LED26.2, LED26.3, R1.2
unnamed: LED26.1, LED26.4, LED27.2, LED27.3
unnamed: LED27.1, LED27.4, LED28.2, LED28.3
unnamed: LED28.1, LED28.4, LED29.2, LED29.3
unnamed: LED29.1, LED29.4, LED30.2, LED30.3
unnamed: 12V5.MP, R1.1, R2.1
unnamed: LED31.2, LED31.3, R2.2
unnamed: LED31.1, LED31.4, LED32.2, LED32.3
unnamed: LED32.1, LED32.4, LED33.2, LED33.3
unnamed: LED33.1, LED33.4, LED34.2, LED34.3
unnamed: LED34.1, LED34.4, LED35.2, LED35.3
unnamed: LED36.2, LED36.3, R3.2
unnamed: LED36.1, LED36.4, LED37.2, LED37.3
unnamed: LED37.1, LED37.4, LED38.2, LED38.3
unnamed: LED38.1, LED38.4, LED39.2, LED39.3
unnamed: LED39.1, LED39.4, LED40.2, LED40.3
unnamed: 12V6.MP, R3.1, R4.1
unnamed: LED41.2, LED41.3, R4.2
unnamed: LED41.1, LED41.4, LED42.2, LED42.3
unnamed: LED42.1, LED42.4, LED43.2, LED43.3
unnamed: LED43.1, LED43.4, LED44.2, LED44.3
unnamed: LED44.1, LED44.4, LED45.2, LED45.3
unnamed: LED46.2, LED46.3, R5.2
unnamed: LED46.1, LED46.4, LED47.2, LED47.3
unnamed: LED47.1, LED47.4, LED48.2, LED48.3
unnamed: LED48.1, LED48.4, LED49.2, LED49.3
unnamed: LED49.1, LED49.4, LED50.2, LED50.3
unnamed: 12V7.MP, R5.1, R6.1
unnamed: LED51.2, LED51.3, R6.2
unnamed: LED51.1, LED51.4, LED52.2, LED52.3
unnamed: LED52.1, LED52.4, LED53.2, LED53.3
unnamed: LED53.1, LED53.4, LED54.2, LED54.3
unnamed: LED54.1, LED54.4, LED55.2, LED55.3
unnamed: LED56.2, LED56.3, R7.2
unnamed: LED56.1, LED56.4, LED57.2, LED57.3
unnamed: LED57.1, LED57.4, LED58.2, LED58.3
unnamed: LED58.1, LED58.4, LED59.2, LED59.3
unnamed: LED59.1, LED59.4, LED60.2, LED60.3
unnamed: 12V8.MP, R7.1, R8.1
unnamed: LED61.2, LED61.3, R8.2
unnamed: LED61.1, LED61.4, LED62.2, LED62.3
unnamed: LED62.1, LED62.4, LED63.2, LED63.3
unnamed: LED63.1, LED63.4, LED64.2, LED64.3
unnamed: LED64.1, LED64.4, LED65.2, LED65.3
RESET1: IC1.39, INPUT.8, OUTPUT.8, RESET1_SELECT.1
RESET2: INPUT.9, OUTPUT.9, RESET2_SELECT.2
RESET3: IC2.39, INPUT1.8, OUTPUT1.8, RESET1_SELECT1.1
RESET4: INPUT1.9, OUTPUT1.9, RESET2_SELECT1.2
RESET5: IC3.39, INPUT2.8, OUTPUT2.8, RESET1_SELECT2.1
RESET6: INPUT2.9, OUTPUT2.9, RESET2_SELECT2.2
RESET_SLCT: RESET1_SELECT.2, RESET2_SELECT.1
RESET_SLCT1: RESET1_SELECT1.2, RESET2_SELECT1.1
RESET_SLCT2: RESET1_SELECT2.2, RESET2_SELECT2.1
SCL: IC1.37, INPUT.4, OUTPUT.4
SCL1: IC2.37, INPUT1.4, OUTPUT1.4
SCL2: IC3.37, INPUT2.4, OUTPUT2.4
SI: IC1.36, INPUT.3, OUTPUT.3
SI1: IC2.36, INPUT1.3, OUTPUT1.3
SI2: IC3.36, INPUT2.3, OUTPUT2.3
